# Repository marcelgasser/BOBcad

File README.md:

# BOBcad
Bee Observer inspired KiCad project for hive monitoring

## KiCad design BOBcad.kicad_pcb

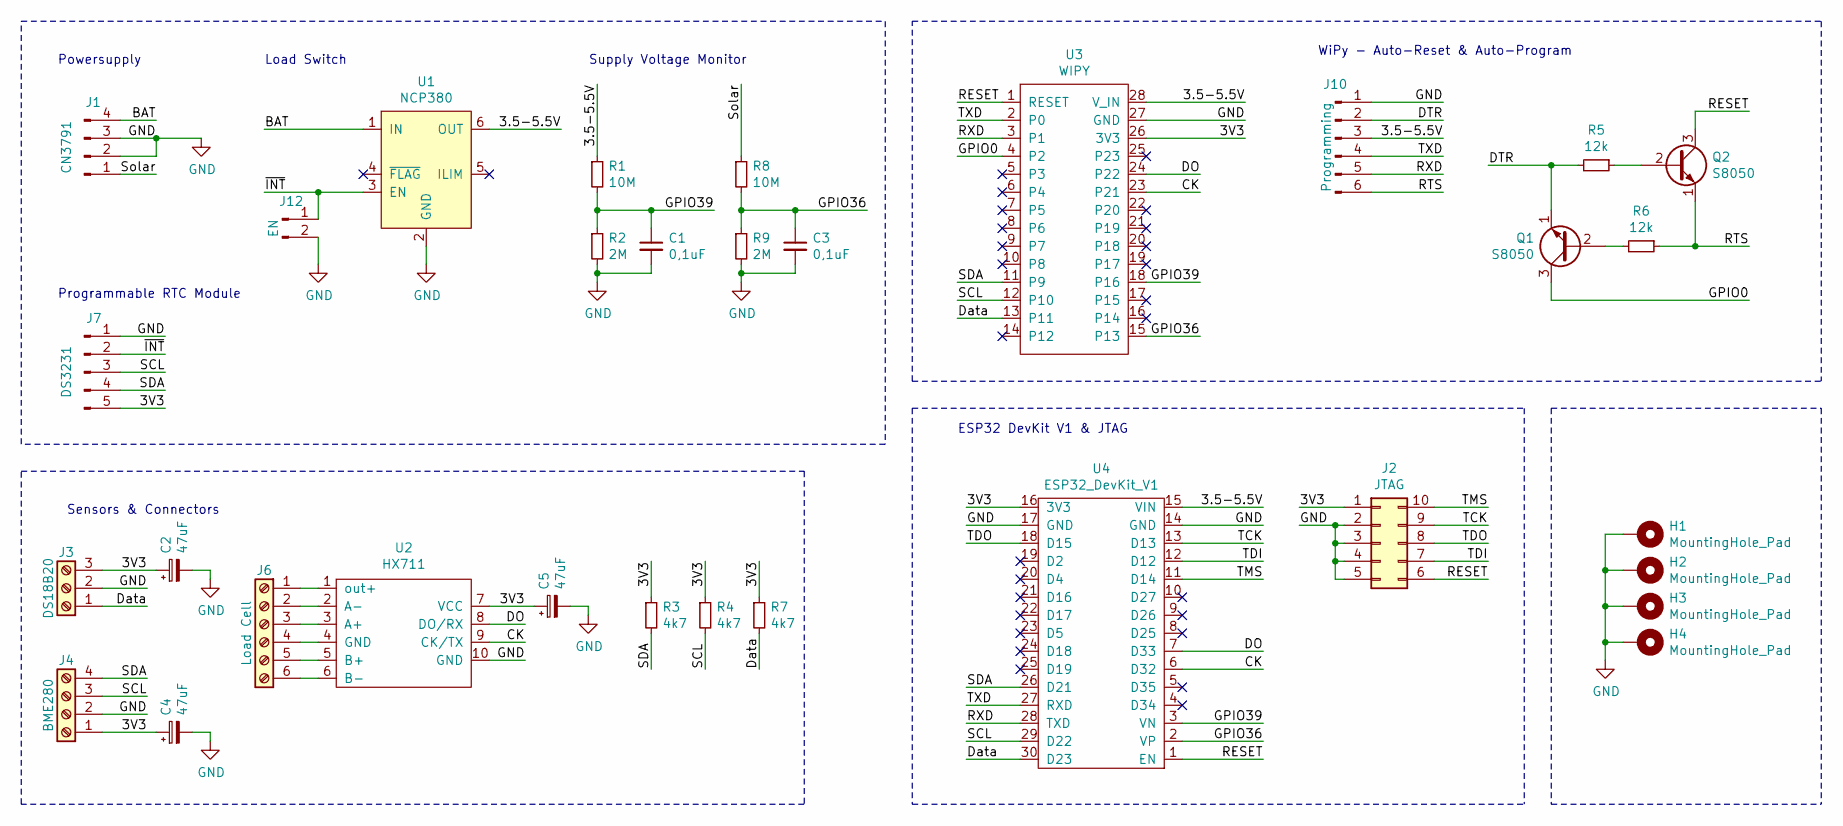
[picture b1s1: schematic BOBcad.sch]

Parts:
C1, C3: 0,1uF; C_0805_HandSoldering; MFG P/N 399-7999-1-ND
C2, C4, C5: 47uF; CP_Radial_D4.0mm_P1.50mm; MFG P/N 493-5936-ND
H1, H2, H3, H4: MountingHole_Pad; MountingHole_3.2mm_M3_Pad
J1: CN3791; CN3791_Module
J2: JTAG; Pin_Header_Straight_2x05_Pitch1.27mm
J3: DS18B20; TerminalBlock_bornier-3_P5.08mm
J4: BME280; TerminalBlock_bornier-4_P5.08mm
J6: Load Cell; TerminalBlock_bornier-6_P5.08mm
J7: DS3231; DS3231mini
J10: Programming; Pin_Header_Straight_1x06_Pitch2.54mm
J12: EN; Pin_Header_Straight_1x02_Pitch2.54mm
Q1, Q2: S8050; SOT-23; MFG P/N MMSS8050-H-TPMSCT-ND
R1, R8: 10M; R_0805_HandSoldering; MFG P/N 311-10.0MCRCT-ND
R2, R9: 2M; R_0805_HandSoldering; MFG P/N 311-2.00MCRCT-ND
R3, R4, R7: 4k7; R_0805_HandSoldering; MFG P/N 311-4.70KCRCT-ND
R5, R6: 12k; R_0805_HandSoldering; MFG P/N 311-12.0KCRCT-ND
U1: NCP380; TSOP-6_1.65x3.05mm_Pitch0.95mm; MFG P/N NCP380HSNAJAAT1G
U2: HX711; HX711_module
U3: WIPY; WiPy_module; MFG P/N 1871-1000-ND
U4: ESP32_DevKit_V1

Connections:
/3.5-5.5V: J10.3, R1.1, U1.6 (OUT), U3.28 (V_IN), U4.15 (VIN)
/3V3: C2.1, C4.1, C5.1, J2.1, J3.3, J4.1, J7.5, R3.1, R4.1, R7.1, U2.7 (VCC), U3.26 (3V3), U4.16 (3V3)
/BAT: J1.4, U1.1 (IN)
/CK: U2.9 (CK/TX), U3.23 (P21), U4.6 (D32)
/DO: U2.8 (DO/RX), U3.24 (P22), U4.7 (D33)
/DTR: J10.2, Q1.1 (E), R5.2
/Data: J3.1, R7.2, U3.13 (P11), U4.30 (D23)
/GPIO0: Q1.3 (C), U3.4 (P2)
/GPIO36: C3.1, R8.2, R9.1, U3.15 (P13), U4.2 (VP)
/GPIO39: C1.1, R1.2, R2.1, U3.18 (P16), U4.3 (VN)
/RESET: J2.6, Q2.3 (C), U3.1 (RESET), U4.1 (EN)
/RTS: J10.6, Q2.1 (E), R6.1
/RXD: J10.5, U3.3 (P1), U4.28 (TXD)
/SCL: J4.3, J7.3, R4.2, U3.12 (P10), U4.29 (D22)
/SDA: J4.4, J7.4, R3.2, U3.11 (P9), U4.26 (D21)
/Solar: J1.1, R8.1
/TCK: J2.9, U4.13 (D13)
/TDI: J2.7, U4.12 (D12)
/TDO: J2.8, U4.18 (D15)
/TMS: J2.10, U4.11 (D14)
/TXD: J10.4, U3.2 (P0), U4.27 (RXD)
/~INT: J7.2, J12.1, U1.3 (EN)
GND: C1.2, C2.2, C3.2, C4.2, C5.2, H1.1, H2.1, H3.1, H4.1, J1.2, J1.3, J2.2, J2.3, J2.4, J2.5, J3.2, J4.2, J7.1, J10.1, J12.2, R2.2, R9.2, U1.2 (GND), U2.10 (GND), U3.27 (GND), U4.14 (GND), U4.17 (GND)
unnamed: J6.1, U2.1 (out+)
unnamed: J6.2, U2.2 (A-)
unnamed: J6.3, U2.3 (A+)
unnamed: J6.4, U2.4 (GND)
unnamed: J6.5, U2.5 (B+)
unnamed: J6.6, U2.6 (B-)
unnamed: Q1.2 (B), R6.2
unnamed: Q2.2 (B), R5.1

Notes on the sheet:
Powersupply
Programmable RTC Module
Load Switch
Supply Voltage Monitor
WiPy - Auto-Reset & Auto-Program
Sensors & Connectors
ESP32 DevKit V1 & JTAG

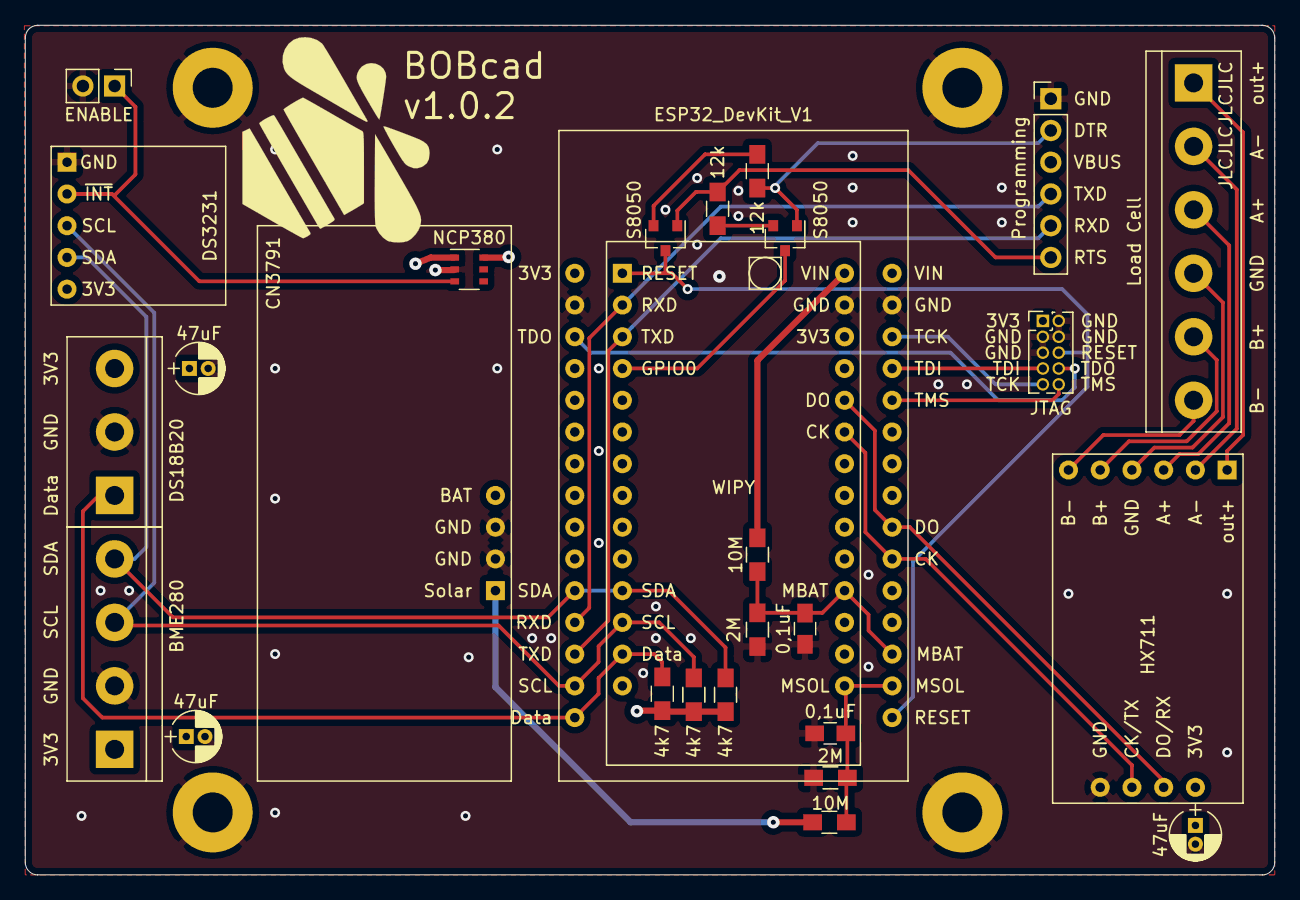
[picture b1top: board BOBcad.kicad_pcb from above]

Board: 4 copper layers, 100.0 x 68.0 mm, 32 parts (0 on the bottom side), 31 nets.

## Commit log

2021-03-23 v1.0.2
    Added solar voltage monitoring
    Modified power plane
    Added two more capacitors for 3v3 lines to sensors
2021-03-23 v1.0.2 gerber files
